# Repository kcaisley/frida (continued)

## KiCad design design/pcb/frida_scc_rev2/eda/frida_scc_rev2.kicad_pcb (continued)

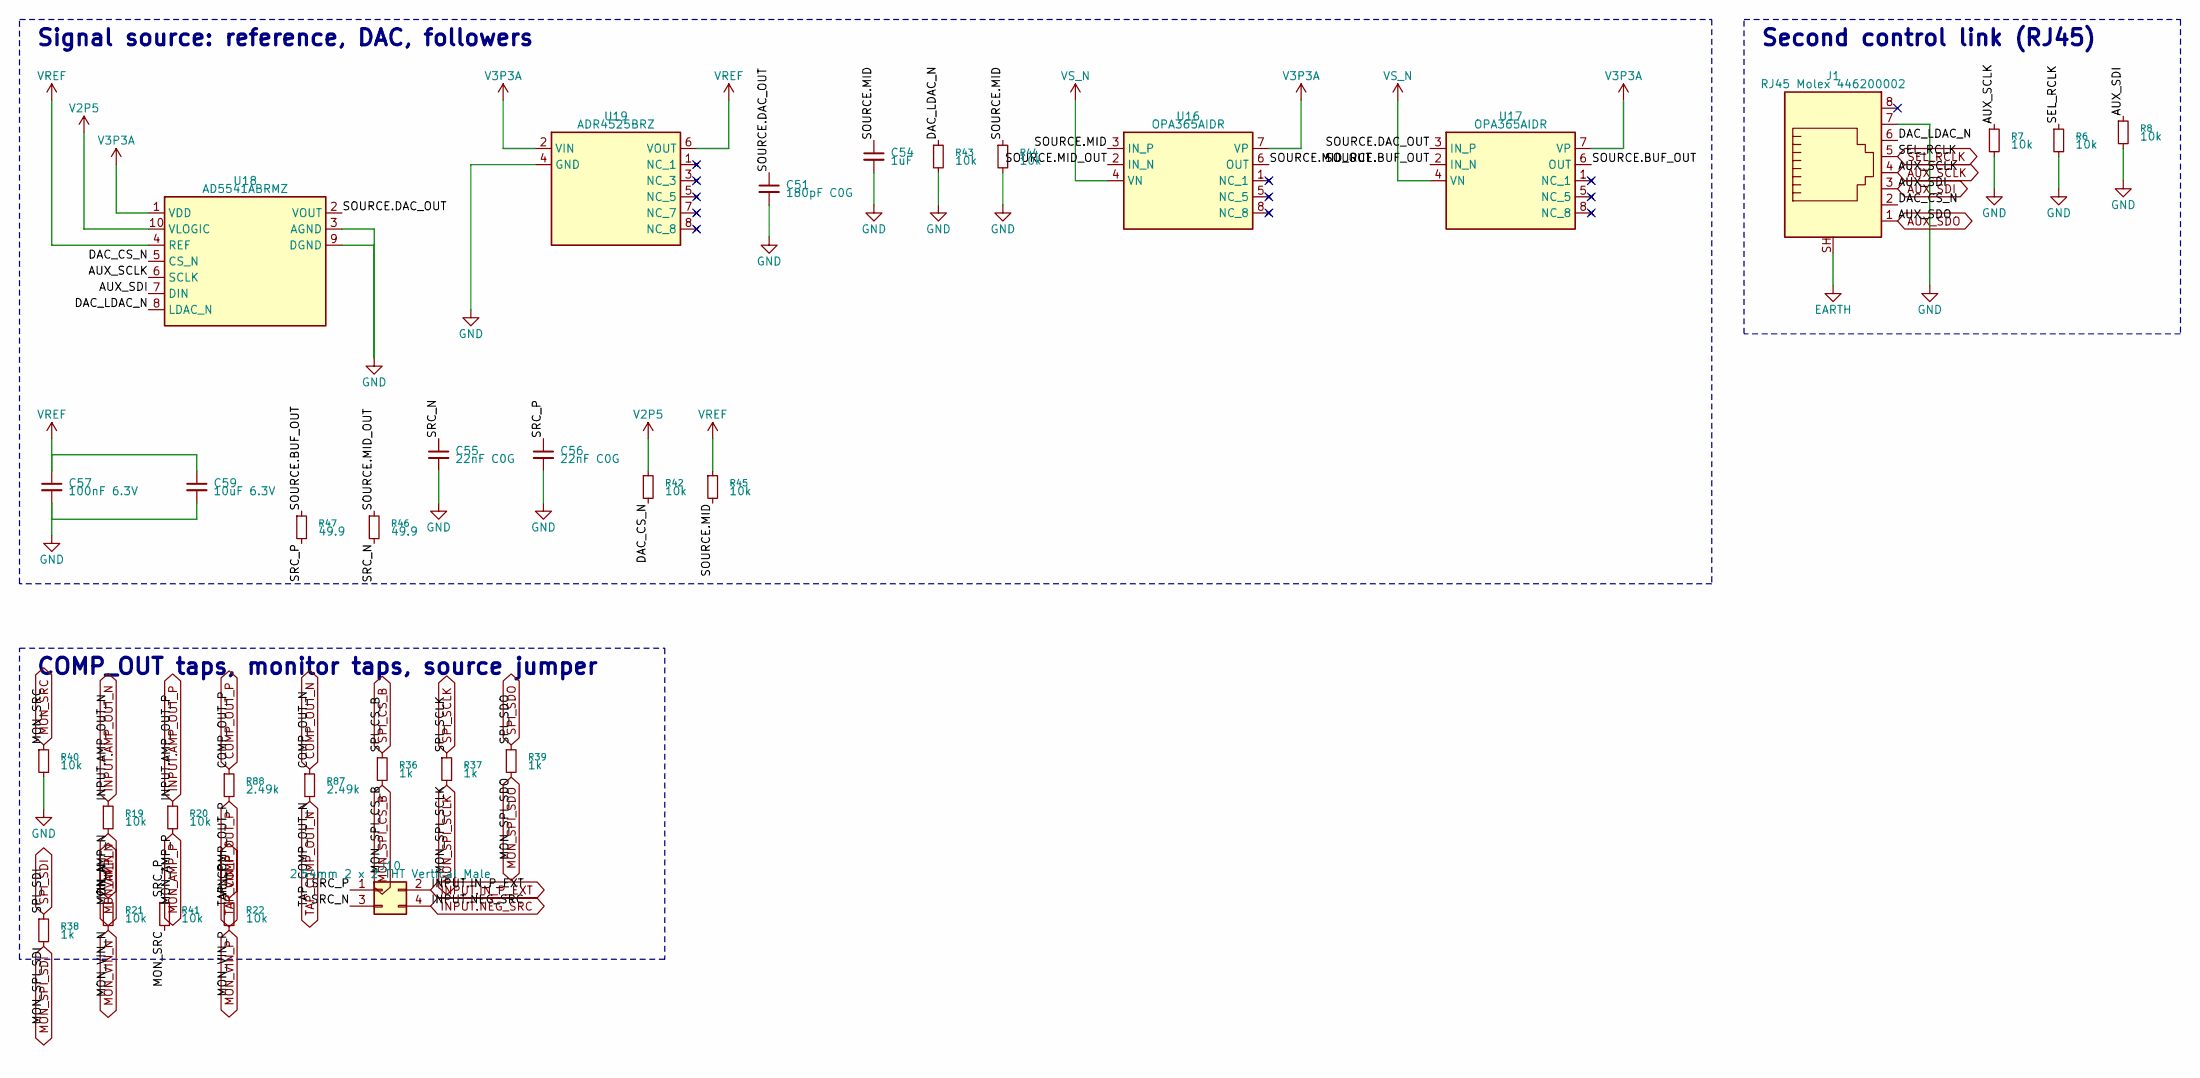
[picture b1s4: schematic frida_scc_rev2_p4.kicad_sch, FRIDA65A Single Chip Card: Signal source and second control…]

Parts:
C51: 180pF C0G; C_0402_1005Metric
C54: 1uF; C_0402_1005Metric
C55, C56: 22nF C0G; C_0805_2012Metric
C57: 100nF 6.3V; C_0402_1005Metric
C59: 10uF 6.3V; C_0805_2012Metric
J1: RJ45 Molex 446200002; Molex_RJ45_446200002
J10: 2.54mm 2 x 2 THT Vertical Male; PinHeader_2x02_P2.54mm_Vertical
R6, R7, R8, R19, R20, R21, R22, R40, R41, R42, R43, R44, R45: 10k; R_0402_1005Metric
R36, R37, R38, R39: 1k; R_0402_1005Metric
R46, R47: 49.9; R_0402_1005Metric
R87, R88: 2.49k; R_0402_1005Metric
U16, U17: OPA365AIDR; SOIC-8_3.9x4.9mm_P1.27mm
U18: AD5541ABRMZ; MSOP-10_3x3mm_P0.5mm
U19: ADR4525BRZ; SOIC-8_3.9x4.9mm_P1.27mm

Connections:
AUX.J_AUX.NC_RJ45_Molex_446200002_8: J1.8
AUX_SCLK: J1.4, R7.1, U18.6 (SCLK); also elsewhere on the board
AUX_SDI: J1.3, R8.1, U18.7 (DIN); also elsewhere on the board
AUX_SDO: J1.1; also elsewhere on the board
COMP_OUT_N: R87.1; also elsewhere on the board
COMP_OUT_P: R88.1; also elsewhere on the board
DAC_CS_N: J1.2, R42.2, U18.5 (CS_N)
DAC_LDAC_N: J1.6, R43.1, U18.8 (LDAC_N)
EARTH: J1.SH; also elsewhere on the board
GND: C51.2, C54.2, C55.2, C56.2, C57.2, C59.2, J1.7, R6.2, R7.2, R8.2, R40.2, R43.2, R44.2, U18.3 (AGND), U18.9 (DGND), U19.4 (GND); also elsewhere on the board
INPUT.AMP_OUT_N: R19.1; also elsewhere on the board
INPUT.AMP_OUT_P: R20.1; also elsewhere on the board
INPUT.IN_P_EXT: J10.2; also elsewhere on the board
INPUT.NEG_SRC: J10.4; also elsewhere on the board
MON_AMP_N: R19.2; also elsewhere on the board
MON_AMP_P: R20.2; also elsewhere on the board
MON_SPI_CS_B: R36.2; also elsewhere on the board
MON_SPI_SCLK: R37.2; also elsewhere on the board
MON_SPI_SDI: R38.2; also elsewhere on the board
MON_SPI_SDO: R39.2; also elsewhere on the board
MON_SRC: R40.1, R41.2; also elsewhere on the board
MON_VIN_N: R21.2; also elsewhere on the board
MON_VIN_P: R22.2; also elsewhere on the board
SEL_RCLK: J1.5, R6.1; also elsewhere on the board
SOURCE.BUF_OUT: R47.1, U17.2 (IN_N), U17.6 (OUT)
SOURCE.DAC_OUT: C51.1, U17.3 (IN_P), U18.2 (VOUT)
SOURCE.MID: C54.1, R44.1, R45.2, U16.3 (IN_P)
SOURCE.MID_OUT: R46.1, U16.2 (IN_N), U16.6 (OUT)
SOURCE.U_BUF_N.NC_OPA365_NC_1: U16.1 (NC_1)
SOURCE.U_BUF_N.NC_OPA365_NC_5: U16.5 (NC_5)
SOURCE.U_BUF_N.NC_OPA365_NC_8: U16.8 (NC_8)
SOURCE.U_BUF_P.NC_OPA365_NC_1: U17.1 (NC_1)
SOURCE.U_BUF_P.NC_OPA365_NC_5: U17.5 (NC_5)
SOURCE.U_BUF_P.NC_OPA365_NC_8: U17.8 (NC_8)
SOURCE.U_REF.NC_ADR4525_NC_1: U19.1 (NC_1)
SOURCE.U_REF.NC_ADR4525_NC_3: U19.3 (NC_3)
SOURCE.U_REF.NC_ADR4525_NC_5: U19.5 (NC_5)
SOURCE.U_REF.NC_ADR4525_NC_7: U19.7 (NC_7)
SOURCE.U_REF.NC_ADR4525_NC_8: U19.8 (NC_8)
SPI_CS_B: R36.1; also elsewhere on the board
SPI_SCLK: R37.1; also elsewhere on the board
SPI_SDI: R38.1; also elsewhere on the board
SPI_SDO: R39.1; also elsewhere on the board
SRC_N: C55.1, J10.3, R46.2
SRC_P: C56.1, J10.1, R41.1, R47.2
TAP_COMP_OUT_N: R87.2; also elsewhere on the board
TAP_COMP_OUT_P: R88.2; also elsewhere on the board
V2P5: R42.1, U18.10 (VLOGIC); also elsewhere on the board
V3P3A: U16.7 (VP), U17.7 (VP), U18.1 (VDD), U19.2 (VIN); also elsewhere on the board
VIN_N: R21.1; also elsewhere on the board
VIN_P: R22.1; also elsewhere on the board
VREF: C57.1, C59.1, R45.1, U18.4 (REF), U19.6 (VOUT)
VS_N: U16.4 (VN), U17.4 (VN); also elsewhere on the board

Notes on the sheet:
Signal source: reference, DAC, followers
Second control link (RJ45)
COMP_OUT taps, monitor taps, source jumper

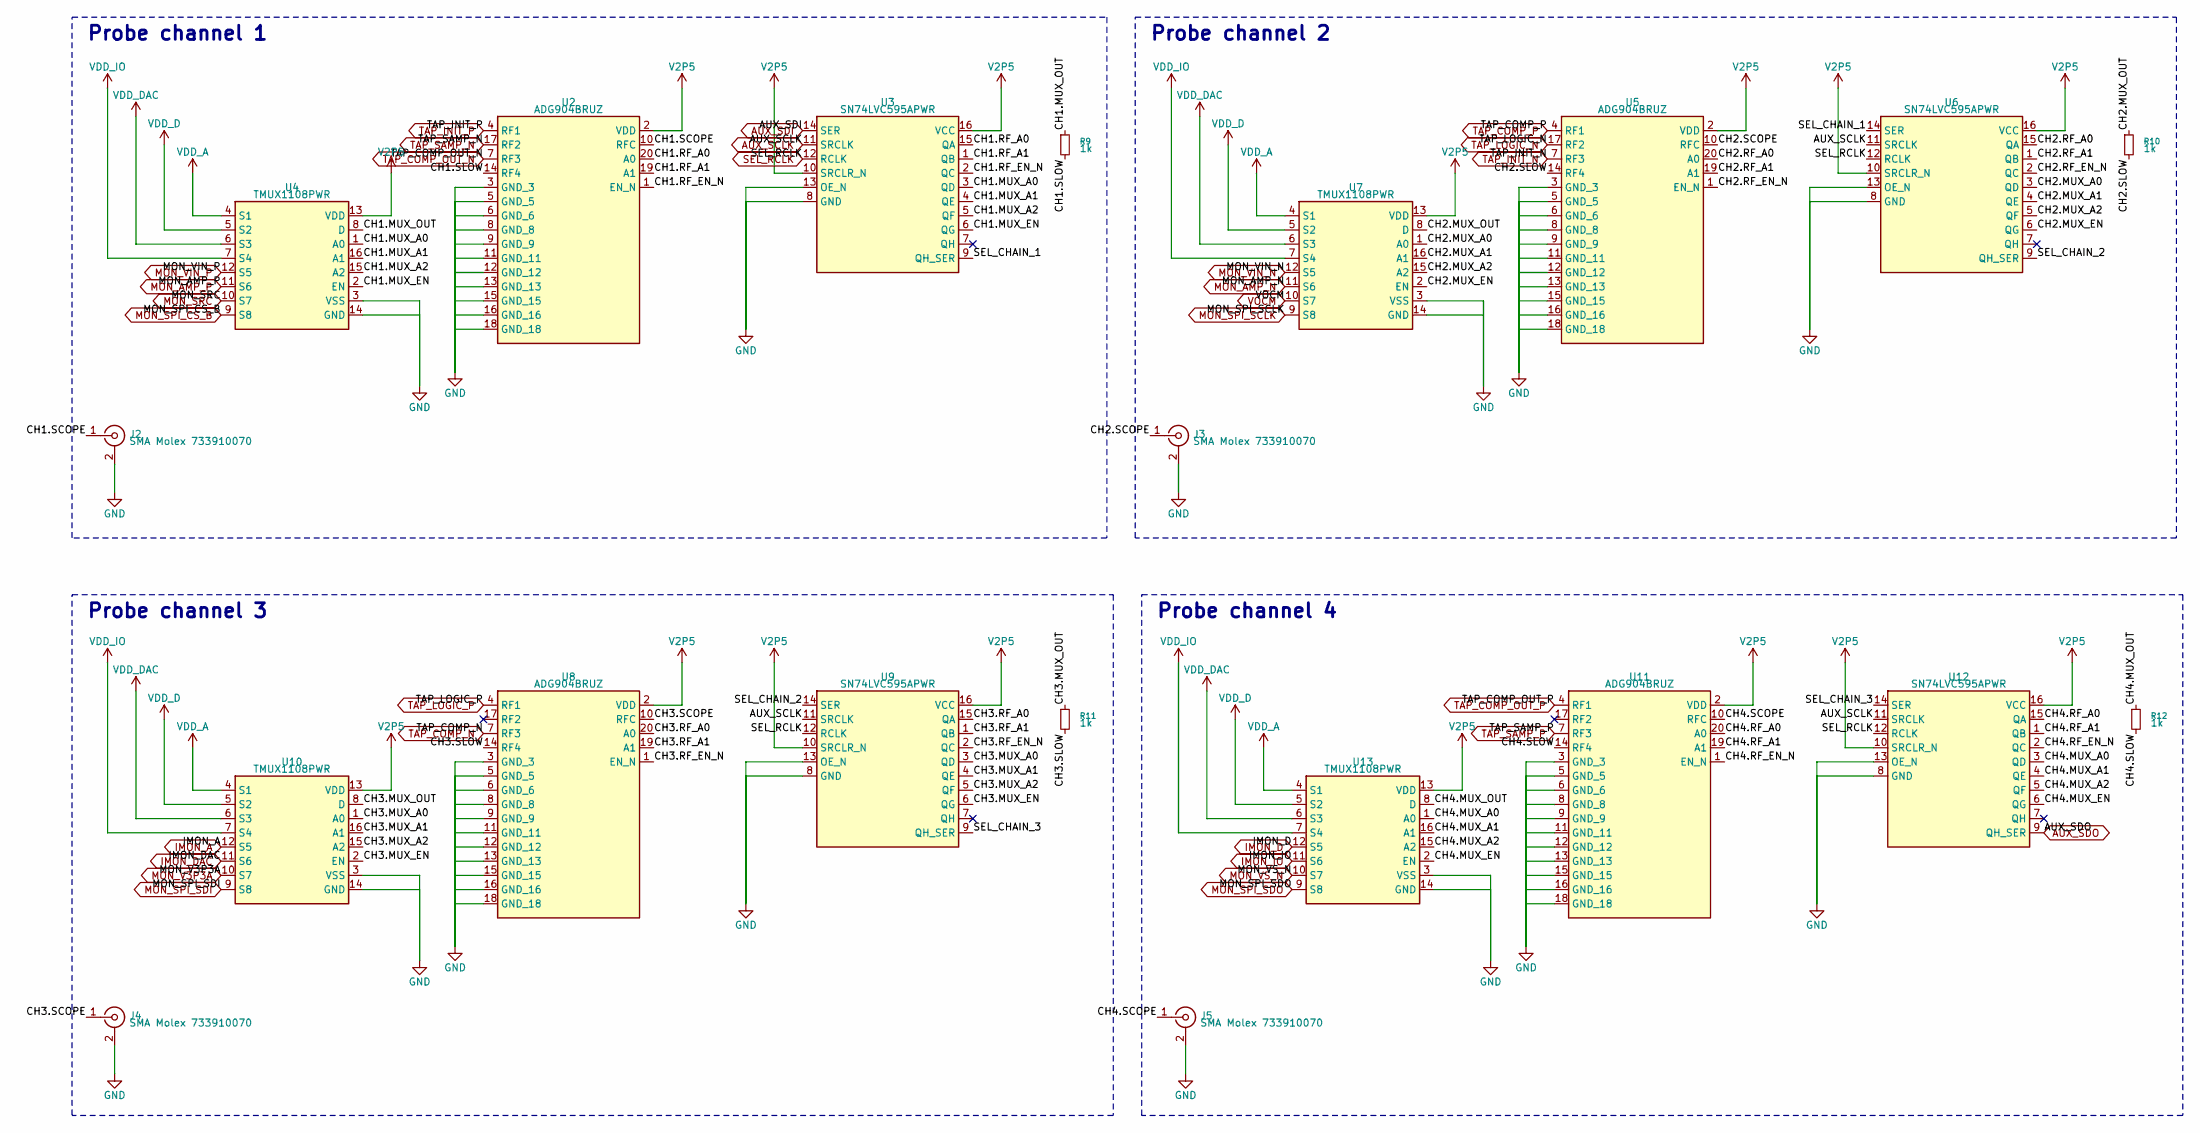
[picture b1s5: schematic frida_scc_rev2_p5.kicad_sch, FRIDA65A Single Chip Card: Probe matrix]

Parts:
J2, J3, J4, J5: SMA Molex 733910070; Molex_SMA_733910070
R9, R10, R11, R12: 1k; R_0402_1005Metric
U2, U5, U8, U11: ADG904BRUZ; TSSOP-20_4.4x6.5mm_P0.65mm
U3, U6, U9, U12: SN74LVC595APWR; TSSOP-16_4.4x5mm_P0.65mm
U4, U7, U10, U13: TMUX1108PWR; TSSOP-16_4.4x5mm_P0.65mm

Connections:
AUX_SCLK: U3.11 (SRCLK), U6.11 (SRCLK), U9.11 (SRCLK), U12.11 (SRCLK); also elsewhere on the board
AUX_SDI: U3.14 (SER); also elsewhere on the board
AUX_SDO: U12.9 (QH_SER); also elsewhere on the board
CH1.MUX_A0: U3.3 (QD), U4.1 (A0)
CH1.MUX_A1: U3.4 (QE), U4.16 (A1)
CH1.MUX_A2: U3.5 (QF), U4.15 (A2)
CH1.MUX_EN: U3.6 (QG), U4.2 (EN)
CH1.MUX_OUT: R9.1, U4.8 (D)
CH1.RF_A0: U2.20 (A0), U3.15 (QA)
CH1.RF_A1: U2.19 (A1), U3.1 (QB)
CH1.RF_EN_N: U2.1 (EN_N), U3.2 (QC)
CH1.SCOPE: J2.1 (In), U2.10 (RFC)
CH1.SLOW: R9.2, U2.14 (RF4)
CH1.U_SEL.NC_SN74LVC595A_QH: U3.7 (QH)
CH2.MUX_A0: U6.3 (QD), U7.1 (A0)
CH2.MUX_A1: U6.4 (QE), U7.16 (A1)
CH2.MUX_A2: U6.5 (QF), U7.15 (A2)
CH2.MUX_EN: U6.6 (QG), U7.2 (EN)
CH2.MUX_OUT: R10.1, U7.8 (D)
CH2.RF_A0: U5.20 (A0), U6.15 (QA)
CH2.RF_A1: U5.19 (A1), U6.1 (QB)
CH2.RF_EN_N: U5.1 (EN_N), U6.2 (QC)
CH2.SCOPE: J3.1 (In), U5.10 (RFC)
CH2.SLOW: R10.2, U5.14 (RF4)
CH2.U_SEL.NC_SN74LVC595A_QH: U6.7 (QH)
CH3.MUX_A0: U9.3 (QD), U10.1 (A0)
CH3.MUX_A1: U9.4 (QE), U10.16 (A1)
CH3.MUX_A2: U9.5 (QF), U10.15 (A2)
CH3.MUX_EN: U9.6 (QG), U10.2 (EN)
CH3.MUX_OUT: R11.1, U10.8 (D)
CH3.RF_A0: U8.20 (A0), U9.15 (QA)
CH3.RF_A1: U8.19 (A1), U9.1 (QB)
CH3.RF_EN_N: U8.1 (EN_N), U9.2 (QC)
CH3.SCOPE: J4.1 (In), U8.10 (RFC)
CH3.SLOW: R11.2, U8.14 (RF4)
CH3.U_RF.NC_ADG904_RF2: U8.17 (RF2)
CH3.U_SEL.NC_SN74LVC595A_QH: U9.7 (QH)
CH4.MUX_A0: U12.3 (QD), U13.1 (A0)
CH4.MUX_A1: U12.4 (QE), U13.16 (A1)
CH4.MUX_A2: U12.5 (QF), U13.15 (A2)
CH4.MUX_EN: U12.6 (QG), U13.2 (EN)
CH4.MUX_OUT: R12.1, U13.8 (D)
CH4.RF_A0: U11.20 (A0), U12.15 (QA)
CH4.RF_A1: U11.19 (A1), U12.1 (QB)
CH4.RF_EN_N: U11.1 (EN_N), U12.2 (QC)
CH4.SCOPE: J5.1 (In), U11.10 (RFC)
CH4.SLOW: R12.2, U11.14 (RF4)
CH4.U_RF.NC_ADG904_RF2: U11.17 (RF2)
CH4.U_SEL.NC_SN74LVC595A_QH: U12.7 (QH)
GND: J2.2 (Ext), J3.2 (Ext), J4.2 (Ext), J5.2 (Ext), U2.3 (GND_3), U2.5 (GND_5), U2.6 (GND_6), U2.8 (GND_8), U2.9 (GND_9), U2.11 (GND_11), U2.12 (GND_12), U2.13 (GND_13), U2.15 (GND_15), U2.16 (GND_16), U2.18 (GND_18), U3.8 (GND), U3.13 (OE_N), U4.3 (VSS), U4.14 (GND), U5.3 (GND_3), U5.5 (GND_5), U5.6 (GND_6), U5.8 (GND_8), U5.9 (GND_9), U5.11 (GND_11), U5.12 (GND_12), U5.13 (GND_13), U5.15 (GND_15), U5.16 (GND_16), U5.18 (GND_18), U6.8 (GND), U6.13 (OE_N), U7.3 (VSS), U7.14 (GND), U8.3 (GND_3), U8.5 (GND_5), U8.6 (GND_6), U8.8 (GND_8), U8.9 (GND_9), U8.11 (GND_11), U8.12 (GND_12), U8.13 (GND_13), U8.15 (GND_15), U8.16 (GND_16), U8.18 (GND_18), U9.8 (GND), U9.13 (OE_N), U10.3 (VSS), U10.14 (GND), U11.3 (GND_3), U11.5 (GND_5), U11.6 (GND_6), U11.8 (GND_8), U11.9 (GND_9), U11.11 (GND_11), U11.12 (GND_12), U11.13 (GND_13), U11.15 (GND_15), U11.16 (GND_16), U11.18 (GND_18), U12.8 (GND), U12.13 (OE_N), U13.3 (VSS), U13.14 (GND); also elsewhere on the board
IMON_A: U10.12 (S5); also elsewhere on the board
IMON_D: U13.12 (S5); also elsewhere on the board
IMON_DAC: U10.11 (S6); also elsewhere on the board
IMON_IO: U13.11 (S6); also elsewhere on the board
MON_AMP_N: U7.11 (S6); also elsewhere on the board
MON_AMP_P: U4.11 (S6); also elsewhere on the board
MON_SPI_CS_B: U4.9 (S8); also elsewhere on the board
MON_SPI_SCLK: U7.9 (S8); also elsewhere on the board
MON_SPI_SDI: U10.9 (S8); also elsewhere on the board
MON_SPI_SDO: U13.9 (S8); also elsewhere on the board
MON_SRC: U4.10 (S7); also elsewhere on the board
MON_V3P3A: U10.10 (S7); also elsewhere on the board
MON_VIN_N: U7.12 (S5); also elsewhere on the board
MON_VIN_P: U4.12 (S5); also elsewhere on the board
MON_VS_N: U13.10 (S7); also elsewhere on the board
SEL_CHAIN_1: U3.9 (QH_SER), U6.14 (SER)
SEL_CHAIN_2: U6.9 (QH_SER), U9.14 (SER)
SEL_CHAIN_3: U9.9 (QH_SER), U12.14 (SER)
SEL_RCLK: U3.12 (RCLK), U6.12 (RCLK), U9.12 (RCLK), U12.12 (RCLK); also elsewhere on the board
TAP_COMP_N: U8.7 (RF3); also elsewhere on the board
TAP_COMP_OUT_N: U2.7 (RF3); also elsewhere on the board
TAP_COMP_OUT_P: U11.4 (RF1); also elsewhere on the board
TAP_COMP_P: U5.4 (RF1); also elsewhere on the board
TAP_INIT_N: U5.7 (RF3); also elsewhere on the board
TAP_INIT_P: U2.4 (RF1); also elsewhere on the board
TAP_LOGIC_N: U5.17 (RF2); also elsewhere on the board
TAP_LOGIC_P: U8.4 (RF1); also elsewhere on the board
TAP_SAMP_N: U2.17 (RF2); also elsewhere on the board
TAP_SAMP_P: U11.7 (RF3); also elsewhere on the board
V2P5: U2.2 (VDD), U3.10 (SRCLR_N), U3.16 (VCC), U4.13 (VDD), U5.2 (VDD), U6.10 (SRCLR_N), U6.16 (VCC), U7.13 (VDD), U8.2 (VDD), U9.10 (SRCLR_N), U9.16 (VCC), U10.13 (VDD), U11.2 (VDD), U12.10 (SRCLR_N), U12.16 (VCC), U13.13 (VDD); also elsewhere on the board
VDD_A: U4.4 (S1), U7.4 (S1), U10.4 (S1), U13.4 (S1); also elsewhere on the board
VDD_D: U4.5 (S2), U7.5 (S2), U10.5 (S2), U13.5 (S2); also elsewhere on the board
VDD_DAC: U4.6 (S3), U7.6 (S3), U10.6 (S3), U13.6 (S3); also elsewhere on the board
VDD_IO: U4.7 (S4), U7.7 (S4), U10.7 (S4), U13.7 (S4); also elsewhere on the board
VOCM: U7.10 (S7); also elsewhere on the board

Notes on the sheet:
Probe channel 1
Probe channel 2
Probe channel 3
Probe channel 4

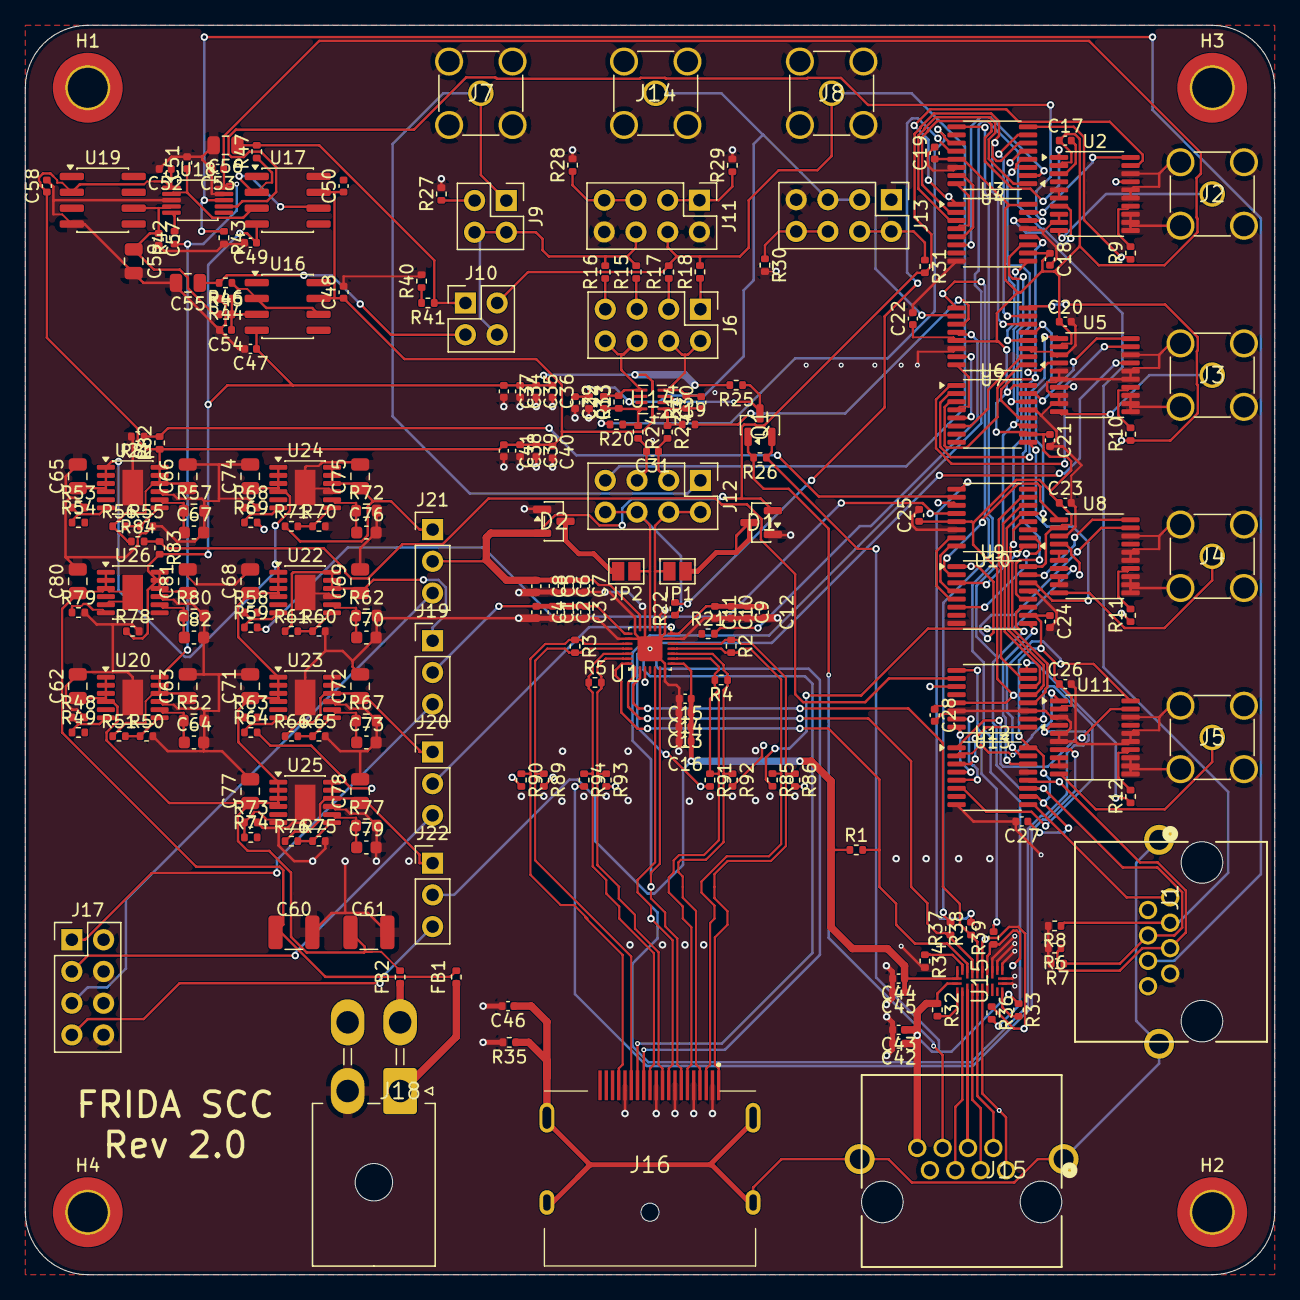
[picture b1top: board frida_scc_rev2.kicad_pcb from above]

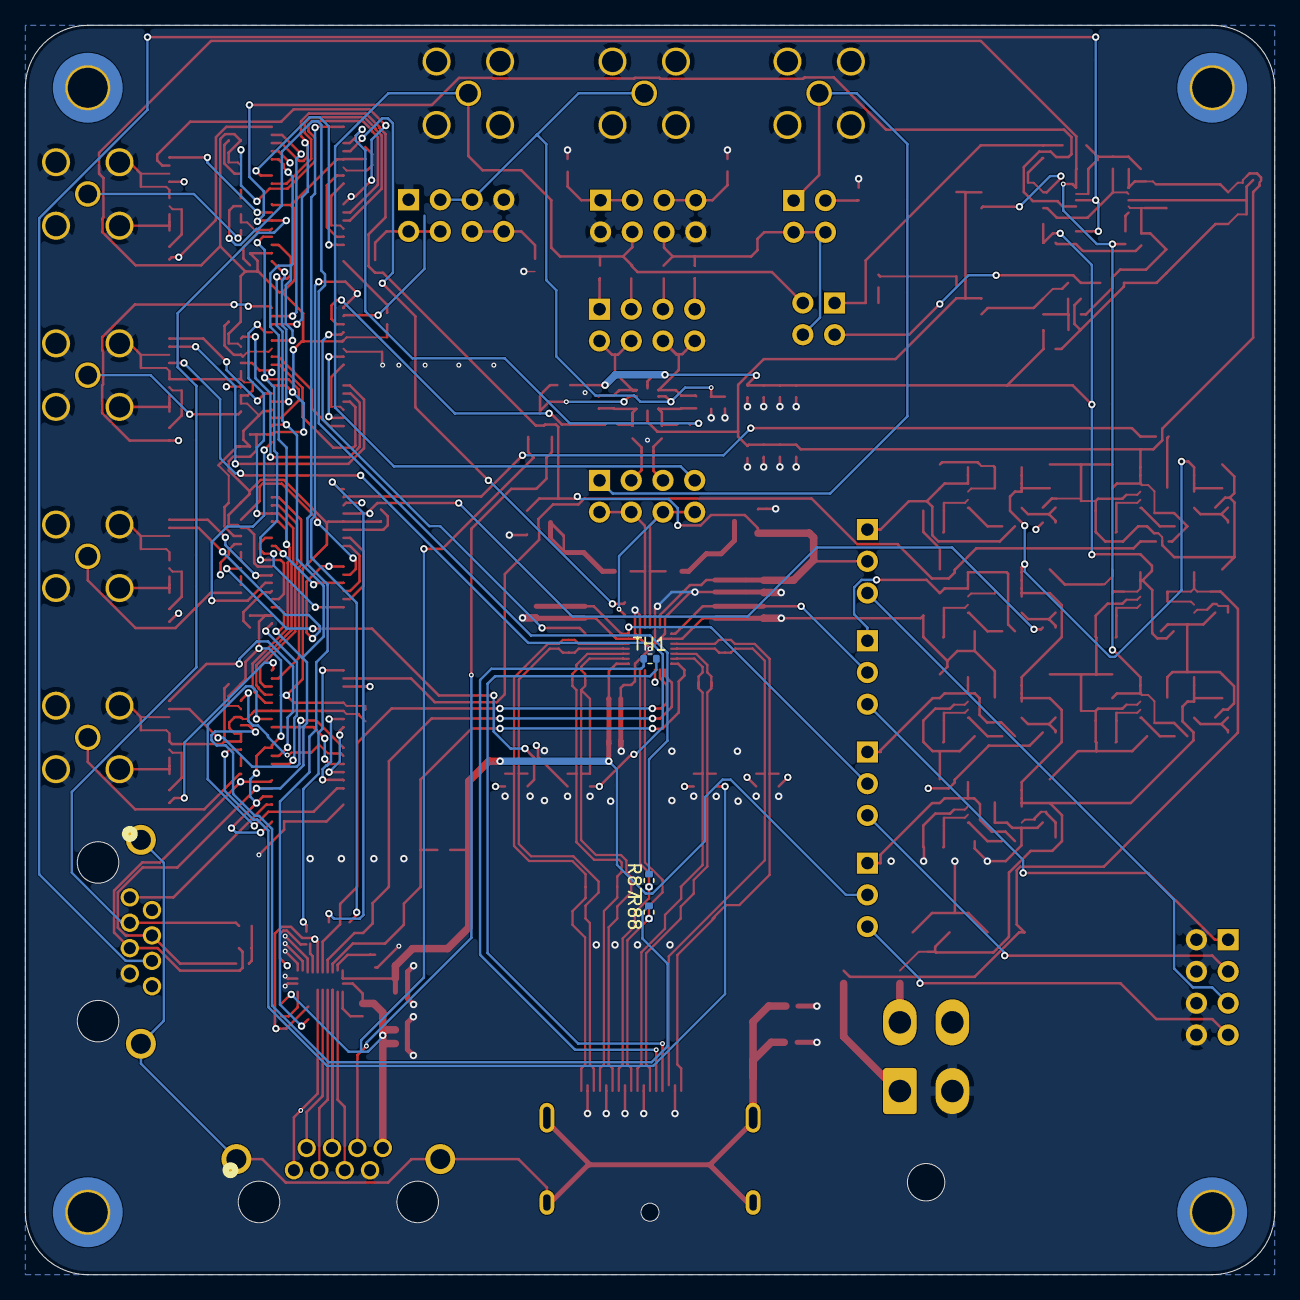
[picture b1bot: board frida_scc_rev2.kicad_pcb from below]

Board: 4 copper layers, 100.0 x 100.0 mm, 236 parts (3 on the bottom side), 173 nets.

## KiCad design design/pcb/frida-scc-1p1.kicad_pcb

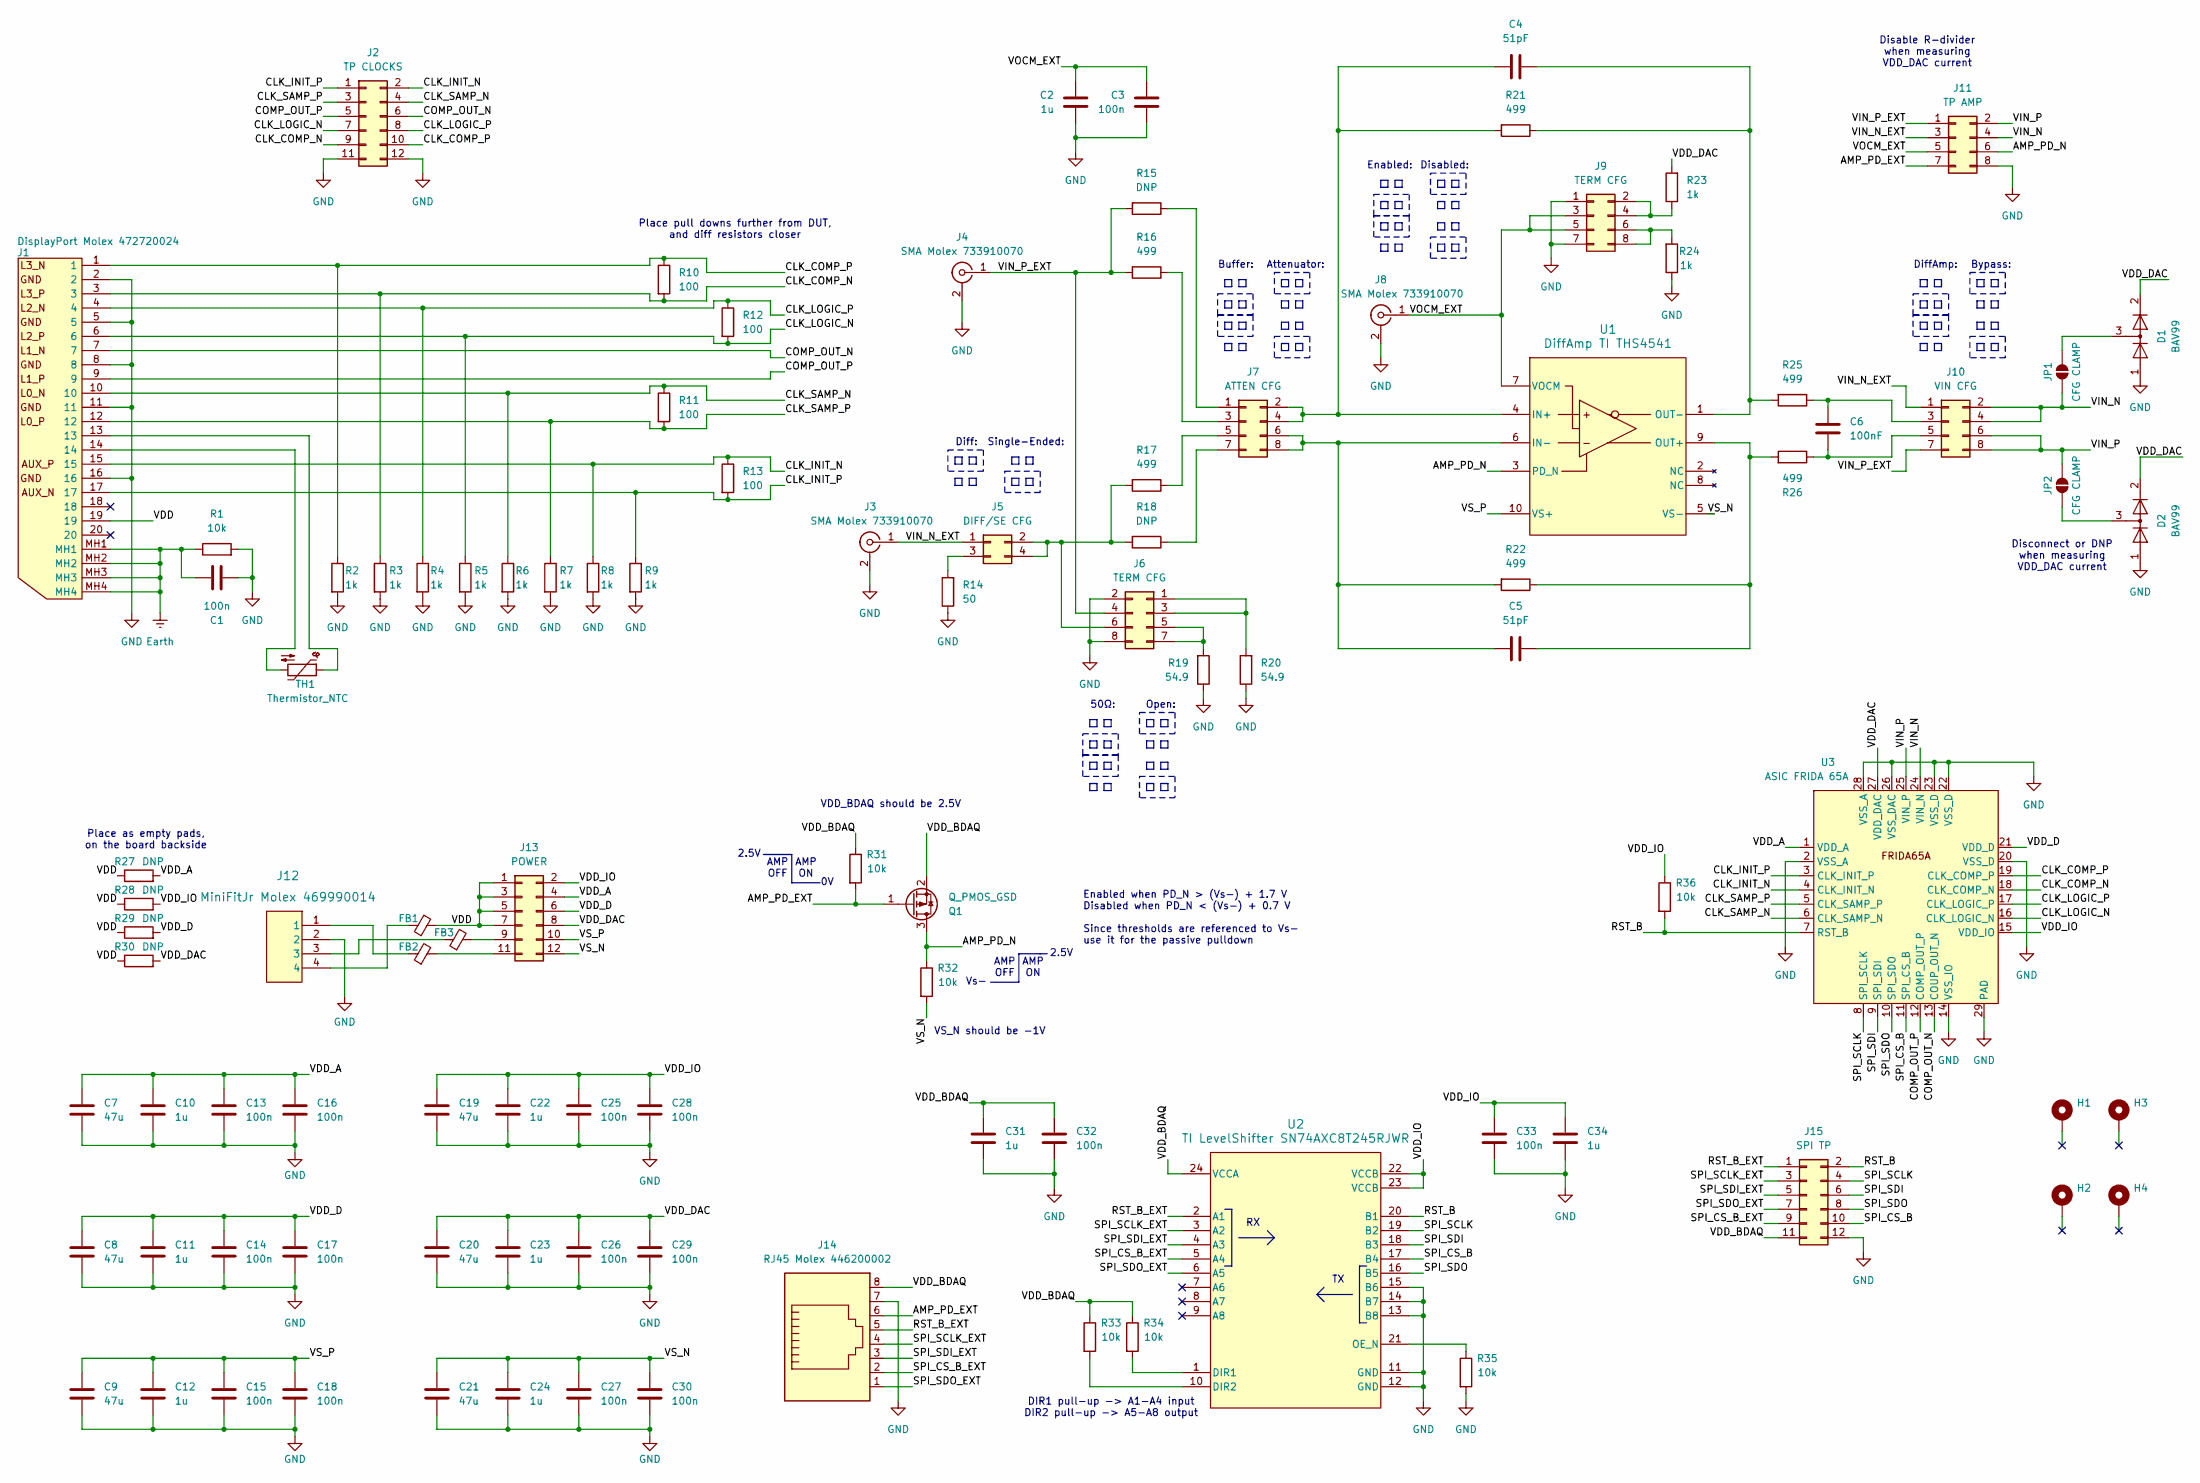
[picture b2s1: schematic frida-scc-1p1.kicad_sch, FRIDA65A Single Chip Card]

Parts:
C1, C3, C13, C14, C15, C16, C17, C18, C25, C26, C27, C28, C29, C30, C32, C33: 100n; C_0402_1005Metric
C2, C10, C11, C12, C22, C23, C24, C31, C34: 1u; C_0402_1005Metric
C4, C5: 51pF; C_0402_1005Metric
C6: 100nF; C_0402_1005Metric
C7, C8, C9, C19, C20, C21: 47u; C_0402_1005Metric
D1, D2: BAV99; SOT-23
FB1, FB2, FB3: FerriteBead_Small; R_0402_1005Metric
H1, H2, H3, H4: MountingHole_Pad; MountingHole_3.2mm_M3_Pad_Via
J1: DisplayPort Molex 472720024; Molex_DisplayPort_472720024; Manufacturer_Part_Number 47272-0024; Mouser Part Number 538-47272-0024
J2: TP CLOCKS; PinHeader_2x06_P2.54mm_Vertical
J3, J4, J8: SMA Molex 733910070; Molex_SMA_733910070
J5: DIFF/SE CFG; PinHeader_2x02_P2.54mm_Vertical
J6, J9: TERM CFG; PinHeader_2x04_P2.54mm_Vertical
J7: ATTEN CFG; PinHeader_2x04_P2.54mm_Vertical
J10: VIN CFG; PinHeader_2x04_P2.54mm_Vertical
J11: TP AMP; PinHeader_2x04_P2.54mm_Vertical
J12: MiniFitJr Molex 469990014; Molex_MiniFitJr_469990014
J13: POWER; PinHeader_2x06_P2.54mm_Vertical
J14: RJ45 Molex 446200002; Molex_RJ45_446200002
J15: SPI TP; PinHeader_2x06_P2.54mm_Vertical
JP1, JP2: CFG CLAMP; SolderJumper-2_P1.3mm_Open_RoundedPad1.0x1.5mm
Q1: Q_PMOS_GSD; SOT-23
R1, R31, R32, R33, R34, R35, R36: 10k; R_0402_1005Metric
R2, R3, R4, R5, R6, R7, R8, R9, R23, R24: 1k; R_0402_1005Metric
R10, R11, R12, R13: 100; R_0402_1005Metric
R14: 50; R_0402_1005Metric
R15, R18: DNP; R_0402_1005Metric
R16, R17, R21, R22, R25, R26: 499; R_0402_1005Metric
R19, R20: 54.9; R_0402_1005Metric
R27, R28, R29, R30: DNP; R_0201_0603Metric
TH1: Thermistor_NTC; R_0402_1005Metric
U1: DiffAmp TI THS4541; TI_DiffAmp_THS4541
U2: TI LevelShifter SN74AXC8T245RJWR; TI_LevelShifter_SN74AXC8T245RJWR
U3: ASIC FRIDA 65A; FRIDA_ASIC_Pad

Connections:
/AMP_PD_EXT: J11.7, J14.6, Q1.1 (G), R31.2
/AMP_PD_N: J11.6, Q1.3 (D), R32.1, U1.3 (PD_N)
/CLK_COMP_N: J1.3, J2.9, R3.1, R10.2, U3.18 (CLK_COMP_N)
/CLK_COMP_P: J1.1, J2.10, R2.1, R10.1, U3.19 (CLK_COMP_P)
/CLK_INIT_N: J1.15, J2.2, R8.1, R13.1, U3.4 (CLK_INIT_N)
/CLK_INIT_P: J1.17, J2.1, R9.1, R13.2, U3.3 (CLK_INIT_P)
/CLK_LOGIC_N: J1.6, J2.7, R5.1, R12.2, U3.16 (CLK_LOGIC_N)
/CLK_LOGIC_P: J1.4, J2.8, R4.1, R12.1, U3.17 (CLK_LOGIC_P)
/CLK_SAMP_N: J1.10, J2.4, R6.1, R11.1, U3.6 (CLK_SAMP_N)
/CLK_SAMP_P: J1.12, J2.3, R7.1, R11.2, U3.5 (CLK_SAMP_P)
/COMP_OUT_N: J1.7, J2.6, U3.13 (COUP_OUT_N)
/COMP_OUT_P: J1.9, J2.5, U3.12 (COMP_OUT_P)
/RST_B: J15.2, R36.2, U2.20 (B1), U3.7 (RST_B)
/RST_B_EXT: J14.5, J15.1, U2.2 (A1)
/SPI_CS_B: J15.10, U2.17 (B4), U3.11 (SPI_CS_B)
/SPI_CS_B_EXT: J14.2, J15.9, U2.5 (A4)
/SPI_SCLK: J15.4, U2.19 (B2), U3.8 (SPI_SCLK)
/SPI_SCLK_EXT: J14.4, J15.3, U2.3 (A2)
/SPI_SDI: J15.6, U2.18 (B3), U3.9 (SPI_SDI)
/SPI_SDI_EXT: J14.3, J15.5, U2.4 (A3)
/SPI_SDO: J15.8, U2.16 (B5), U3.10 (SPI_SDO)
/SPI_SDO_EXT: J14.1, J15.7, U2.6 (A5)
/VDD: FB1.2, J1.19, J13.1, J13.3, J13.5, J13.7, R27.1, R28.1, R29.1, R30.1
/VDD_A: C7.1, C10.1, C13.1, C16.1, J13.4, R27.2, U3.1 (VDD_A)
/VDD_BDAQ: C31.1, C32.1, J14.8, J15.11, Q1.2 (S), R31.1, R33.1, R34.1, U2.24 (VCCA)
/VDD_D: C8.1, C11.1, C14.1, C17.1, J13.6, R29.2, U3.21 (VDD_D)
/VDD_DAC: C20.1, C23.1, C26.1, C29.1, D1.2 (A), D2.2 (A), J13.8, R23.2, R30.2, U3.27 (VDD_DAC)
/VDD_IO: C19.1, C22.1, C25.1, C28.1, C33.1, C34.1, J13.2, R28.2, R36.1, U2.22 (VCCB), U2.23 (VCCB), U3.15 (VDD_IO)
/VIN_N: J10.2, J10.4, J11.4, JP1.2 (B), U3.24 (VIN_N)
/VIN_N_EXT: J3.1 (In), J5.1, J10.1, J11.3
/VIN_P: J10.6, J10.8, J11.2, JP2.1 (A), U3.25 (VIN_P)
/VIN_P_EXT: J4.1 (In), J6.4, J10.7, J11.1, R15.2, R16.2
/VOCM_EXT: C2.1, C3.1, J8.1 (In), J9.3, J9.5, J11.5, U1.7 (VOCM)
/VS_N: C21.1, C24.1, C27.1, C30.1, J13.12, R32.2, U1.5 (VS-)
/VS_P: C9.1, C12.1, C15.1, C18.1, J13.10, U1.10 (VS+)
Earth: C1.1, J1.MH1, J1.MH2, J1.MH3, J1.MH4, R1.1
GND: C1.2, C2.2, C3.2, C7.2, C8.2, C9.2, C10.2, C11.2, C12.2, C13.2, C14.2, C15.2, C16.2, C17.2, C18.2, C19.2, C20.2, C21.2, C22.2, C23.2, C24.2, C25.2, C26.2, C27.2, C28.2, C29.2, C30.2, C31.2, C32.2, C33.2, C34.2, D1.1 (K), D2.1 (K), J1.2, J1.5, J1.8, J1.11, J1.16, J2.11, J2.12, J3.2 (Ext), J4.2 (Ext), J6.2, J6.8, J8.2 (Ext), J9.1, J9.7, J11.8, J12.2, J14.7, J15.12, R1.2, R2.2, R3.2, R4.2, R5.2, R6.2, R7.2, R8.2, R9.2, R14.1, R19.1, R20.1, R24.1, R35.2, U2.11 (GND), U2.12 (GND), U2.13 (B8), U2.14 (B7), U2.15 (B6), U3.2 (VSS_A), U3.14 (VSS_IO), U3.20 (VSS_D), U3.22 (VSS_D), U3.23 (VSS_D), U3.26 (VSS_DAC), U3.28 (VSS_A), U3.29 (PAD)
unnamed: FB1.1, J12.4
unnamed: FB2.1, J12.1
unnamed: FB3.1, J12.3
unnamed: J1.13, TH1.1
unnamed: J1.14, TH1.2
unnamed: J5.2, J5.4, J6.6, R17.2, R18.2
unnamed: J5.3, R14.2
unnamed: J6.1, J6.3, R20.2
unnamed: J6.5, J6.7, R19.2
unnamed: J7.1, R15.1
unnamed: C4.1, J7.2, J7.4, R21.2, U1.4 (IN+)
unnamed: J7.3, R16.1
unnamed: J7.5, R17.1
unnamed: C5.1, J7.6, J7.8, R22.2, U1.6 (IN-)
unnamed: J7.7, R18.1
unnamed: J9.2, J9.4, R23.1
unnamed: J9.6, J9.8, R24.2
unnamed: C6.1, J10.3, R25.1
unnamed: C6.2, J10.5, R26.1
unnamed: FB3.2, J13.9
unnamed: FB2.2, J13.11
unnamed: D1.3 (K), JP1.1 (A)
unnamed: D2.3 (K), JP2.2 (B)
unnamed: C5.2, R22.1, R26.2, U1.9 (OUT+)
unnamed: C4.2, R21.1, R25.2, U1.1 (OUT-)
unnamed: R34.2, U2.1 (DIR1)
unnamed: R33.2, U2.10 (DIR2)
unnamed: R35.1, U2.21 (OE_N)

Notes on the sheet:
2.5V
Vs-
Bypass:
DiffAmp:
Single-Ended:
Disable R-divider when measuring VDD_DAC current
AMP ON
Disconnect or DNP when measuring VDD_DAC current
Enabled when PD_N > (Vs-) + 1.7 V Disabled when PD_N < (Vs-) + 0.7 V Since thresholds are referenced to Vs- use it for the passive pulldown
Open:
Attenuator:
Place as empty pads, on the board backside
DIR1 pull-up -> A1-A4 input DIR2 pull-up -> A5-A8 output
50Ω:
Enabled:
VDD_BDAQ should be 2.5V
Diff:
Place pull downs further from DUT, and diff resistors closer
VS_N should be -1V
AMP OFF
Disabled:
Buffer:
